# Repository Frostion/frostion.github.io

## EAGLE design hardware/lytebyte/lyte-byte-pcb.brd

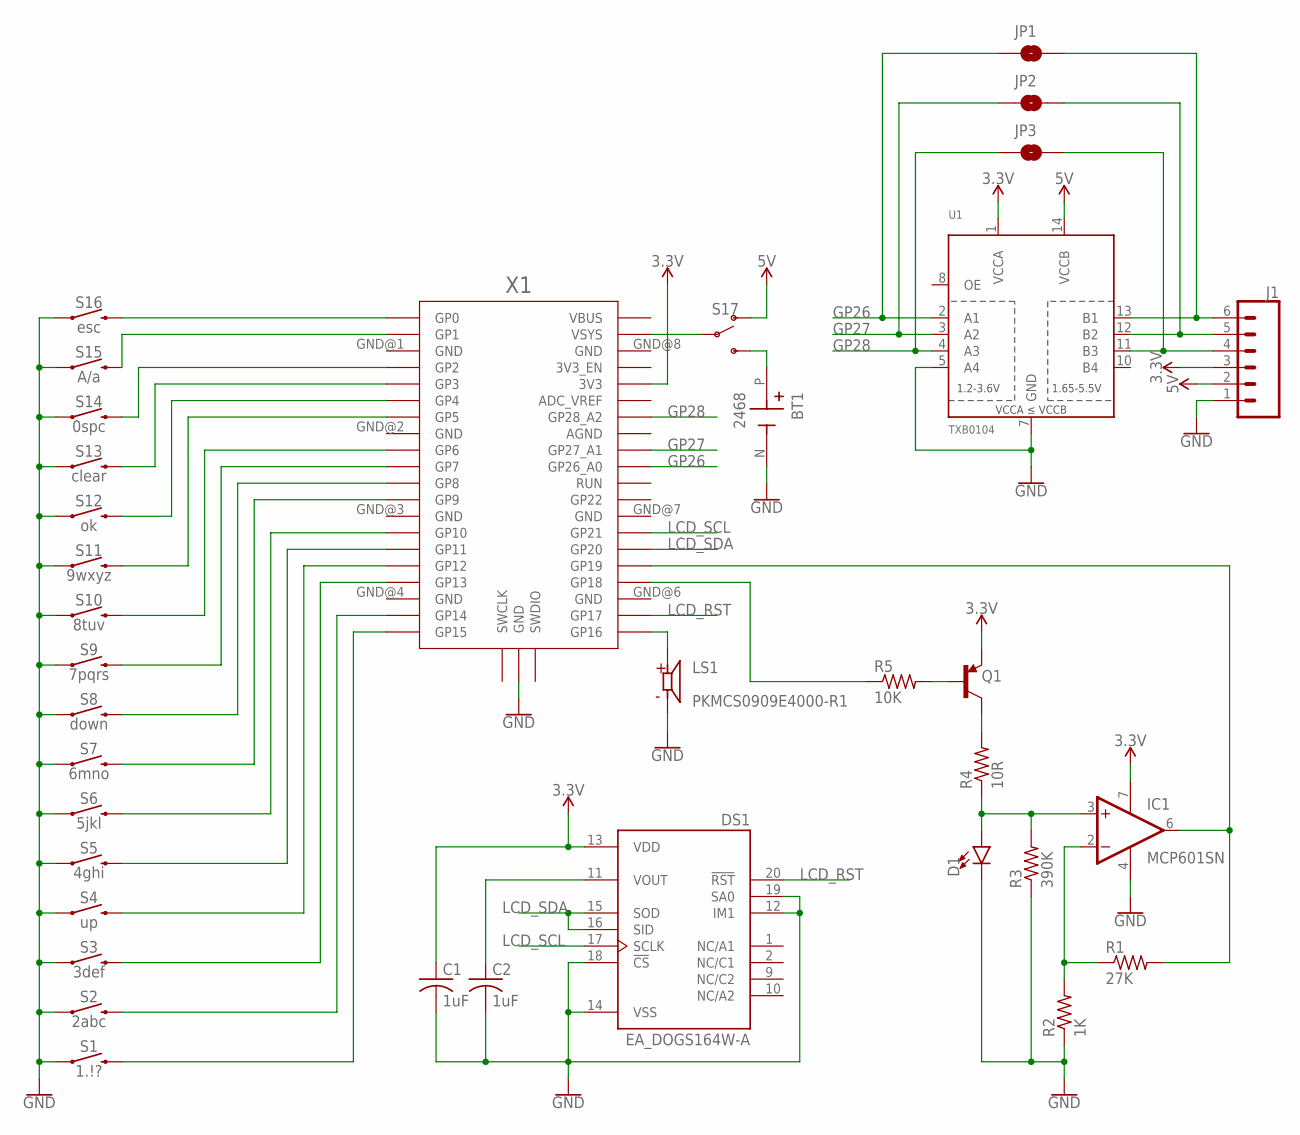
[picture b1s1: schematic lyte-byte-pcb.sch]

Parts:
BT1: 2468; BAT_2468
C1, C2: 1uF; C1206
D1: LED5MM; LED_5MM
DS1: EA_DOGS164W-A; LCD_EA_DOGS164W-A
IC1: MCP601SN; SO08
J1: CONN_06SILK_FEMALE_PTH; 1X06
JP1, JP2, JP3: JUMPER-SMT_2_NO_NO-SILK; SMT-JUMPER_2_NO_NO-SILK
LS1: PKMCS0909E4000-R1; SPKR_PKMCS0909E4000-R1
Q1: TRANS_PNP-PMBT3906|MMBT3906L; SOT23-3
R1: 27K; R1206
R2: 1K; R1206
R3: 390K; R1206
R4: 10R; R1206
R5: 10K; R1206
S1: 1.\!?; TACTILE_SWITCH_SMD_5.2MM
S2: 2abc; TACTILE_SWITCH_SMD_5.2MM
S3: 3def; TACTILE_SWITCH_SMD_5.2MM
S4: up; TACTILE_SWITCH_SMD_5.2MM
S5: 4ghi; TACTILE_SWITCH_SMD_5.2MM
S6: 5jkl; TACTILE_SWITCH_SMD_5.2MM
S7: 6mno; TACTILE_SWITCH_SMD_5.2MM
S8: down; TACTILE_SWITCH_SMD_5.2MM
S9: 7pqrs; TACTILE_SWITCH_SMD_5.2MM
S10: 8tuv; TACTILE_SWITCH_SMD_5.2MM
S11: 9wxyz; TACTILE_SWITCH_SMD_5.2MM
S12: ok; TACTILE_SWITCH_SMD_5.2MM
S13: clear; TACTILE_SWITCH_SMD_5.2MM
S14: 0spc; TACTILE_SWITCH_SMD_5.2MM
S15: A/a; TACTILE_SWITCH_SMD_5.2MM
S16: esc; TACTILE_SWITCH_SMD_5.2MM
S17: SWITCH-SPDT-SMD-AYZ0202; SWITCH_DPDT_SMD_AYZ0202
U1: TXB0104; SO14
X1: RPI_PICO_IG-SMD; RPI_PICO

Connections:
3.3V: C1.1, DS1.13 (VDD), IC1.7 (V+), J1.3, Q1.2 (E), U1.1 (VCCA), X1.3V3
5V: J1.2, S17.1 (O), U1.14 (VCCB)
GND: BT1.N (NEG), C1.2, C2.2, D1.K (C), DS1.12 (IM1), DS1.14 (VSS), DS1.18 (!CS), DS1.19 (SA0), IC1.4 (V-), J1.1, LS1.2 (N), R2.1, R3.1, S1.1, S2.1, S3.1, S4.1, S5.1, S6.1, S7.1, S8.1, S9.1, S10.1, S11.1, S12.1, S13.1, S14.1, S15.1, S16.1, U1.5 (A4), U1.7 (GND), X1.GND@5 (GND)
GP26: JP1.1, U1.2 (A1), X1.GP26_A0
GP27: JP2.1, U1.3 (A2), X1.GP27_A1
GP28: JP3.1, U1.4 (A3), X1.GP28_A2
LCD_RST: DS1.20 (!RST), X1.GP17
LCD_SCL: DS1.17 (SCLK), X1.GP21
LCD_SDA: DS1.15 (SOD), DS1.16 (SID), X1.GP20
LED_TX: IC1.6 (OUT), R1.2, X1.GP19
unnamed: S16.3 (2), X1.GP0
unnamed: S15.3 (2), X1.GP1
unnamed: S14.3 (2), X1.GP2
unnamed: S13.3 (2), X1.GP3
unnamed: S12.3 (2), X1.GP4
unnamed: S11.3 (2), X1.GP5
unnamed: S10.3 (2), X1.GP6
unnamed: S9.3 (2), X1.GP7
unnamed: S8.3 (2), X1.GP8
unnamed: S7.3 (2), X1.GP9
unnamed: S6.3 (2), X1.GP10
unnamed: S5.3 (2), X1.GP11
unnamed: S4.3 (2), X1.GP12
unnamed: S3.3 (2), X1.GP13
unnamed: S2.3 (2), X1.GP14
unnamed: S1.3 (2), X1.GP15
unnamed: C2.1, DS1.11 (VOUT)
unnamed: Q1.1 (B), R5.2
unnamed: Q1.3 (C), R4.2
unnamed: D1.A, IC1.3 (+IN), R3.2, R4.1
unnamed: BT1.P (POS), S17.3 (S)
unnamed: IC1.2 (-IN), R1.1, R2.2
unnamed: S17.2, X1.VSYS
unnamed: R5.1, X1.GP18
unnamed: J1.6, JP1.2, U1.13 (B1)
unnamed: J1.5, JP2.2, U1.12 (B2)
unnamed: J1.4, JP3.2, U1.11 (B3)
unnamed: LS1.1, X1.GP16

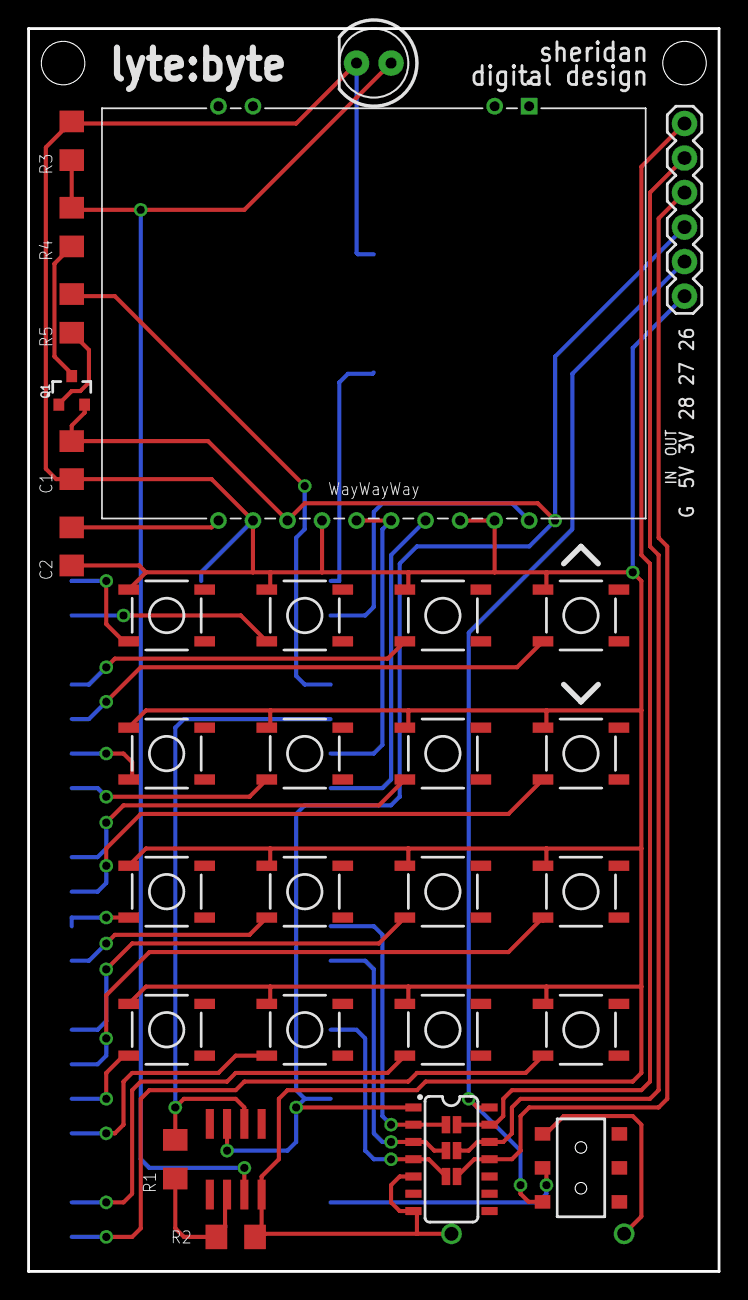
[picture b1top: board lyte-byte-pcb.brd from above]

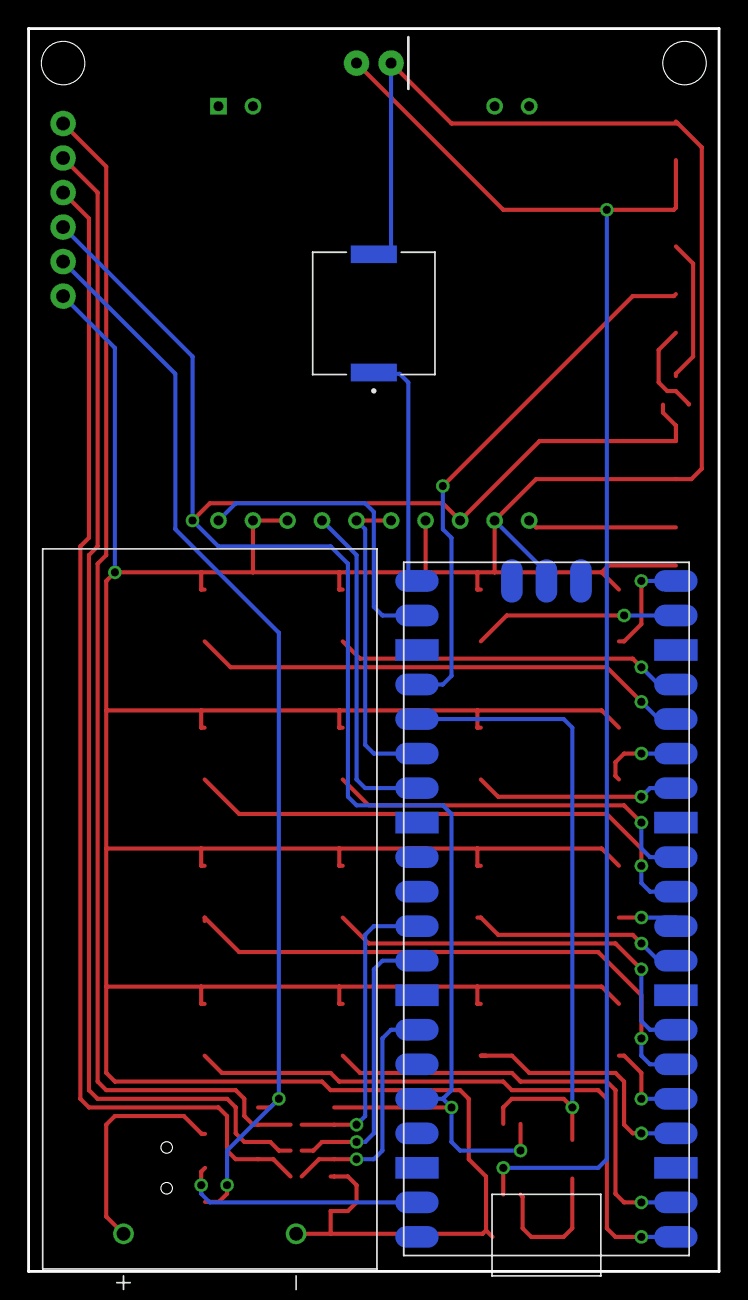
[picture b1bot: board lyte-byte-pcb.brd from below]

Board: 2 copper layers, 50.8 x 91.4 mm, 36 parts (3 on the bottom side), 38 nets.

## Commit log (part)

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2017-02-02 fixxxx
2017-02-02 some GOOD animations now
2017-02-02 github wow
2017-02-02 fixing mistakes github made
2017-02-02 adding CUSTOMIZED placeholders
2017-02-03 no cache
2017-02-03 no caching
2017-02-03 a bit more line height
2017-02-04 Update index.html
    fixed it ;)
2017-02-06 added some table magic
2017-02-06 table magic
2017-02-07 Adding divs
2017-02-07 more div stuff
2017-02-07 Trying to do div stuff
2017-02-07 lets see if this works
2017-02-08 style upgrades
2017-02-13 testing text alignment change
2017-02-13 never mind, going back
2017-02-15 made a page to put other crap in
    man i just have so much content that i needed to make another page for it all
2017-02-15 added "other" link
2017-02-19 uploaded chipwave files
2017-02-21 Starting to add a lil bit of content finally
2017-02-21 holy crap even more content
2017-02-22 i dont even know anymore
2017-02-22 made placeholder page more interesting
2017-02-23 removed direct link to my reddit account
2017-02-23 removed unnecessary page
2017-02-23 I GOT FLEXBOX WORKING YAAAAAAAAY
2017-02-23 mild change
2017-02-23 more mild changes
2017-02-23 SOME WHITESPACE
2017-02-23 a whole bunch of crispy removals
2017-02-23 super cool hover fx
2017-02-24 BETTER placeholder page
2017-02-25 adding content about plushies
2017-02-25 added favicon
2017-02-25 added ratings to plushie page
2017-02-25 added blog link
2017-02-26 A TON OF UPDATES
    Added much more descriptive reviews to the plushies page, and made the
    nav bar work better on smaller screens
2017-02-26 rearranged some pages
    made "plushies and other" page just for plushies, and added a separate
    other page
2017-02-26 added some crap to the "other" page
2017-02-26 better bullet
2017-02-26 new favicon
2017-02-26 newer favicon
2017-02-27 renaming some stuff
2017-02-27 oh god github
2017-02-27 TRYING NEW FONT
2017-02-27 trying another font
2017-02-27 not a good font
2017-02-27 oh god more font
2017-02-27 i think i'm finally there
2017-02-27 removed other page stuff because it was useless
2017-02-27 moved images around
2017-03-01 fresher animations and updates
2017-03-01 un-borked things
2017-03-02 made a nice glow
2017-03-05 better diy synth page layout
2017-03-09 better plushie review layout
    much more readable
2017-03-09 new better pictures and blaziken reivew
2017-03-09 added zoomability to images
2017-03-09 more details
2017-03-10 renamed blaziken image file
2017-03-10 added recommendations to plushie reviews
2017-03-10 removed old images to save memory
2017-03-10 removed crap
2017-03-11 toot
2017-03-11 SLICK NEW homepage
2017-03-11 added buttons to navbar and changed glow
2017-03-12 horizontal rules rule
2017-03-12 RAD NEW BACKGROUND COLORS
2017-03-12 homepage fades in from black now
2017-03-12 made about page bkg more pleasing
2017-03-13 more social media links
2017-03-13 added instagram link
2017-03-13 added a little notification message thing
2017-03-14 notification station test
2017-03-15 removed social media buttons - they were ugly
2017-03-15 removed twitter button
    i dont use twitter
2017-03-15 added a back to top button
2017-03-16 added crap to this page wooooo
2017-03-16 added things i dont like so you can get to know me better
2017-03-16 more things i hate
2017-03-17 more crappppp
2017-03-17 more junk on the about page
2017-03-18 fixed italics
2017-03-18 added padding around images
2017-03-18 cut down on image size
2017-03-19 slightly less ugly green
2017-03-22 changed default text aligns
2017-03-22 changed the look
2017-03-22 removed unneeded align="center"s
2017-03-22 removed unneeded aligns
2017-03-22 woops
2017-03-22 messed up some aligns
2017-03-22 fixed aligns
2017-03-22 added a warning about lack of content
2017-03-28 updated reviews
2017-03-28 review action
2017-03-28 added socially acceptable quotation marks
2017-03-29 why am i doing this
2017-03-29 fixed a mystery parenthesis
2017-03-29 im not ok at grammar
2017-03-31 inches
2017-03-31 added placeholder because IMPATIENT
    COME ON LUCARIO
2017-04-02 new reviews and more images
2017-04-02 removed a gross <hr>
2017-04-02 smaller faster images
2017-04-03 changed some ratings
2017-04-04 added tiny eevee review
2017-04-04 updated palkia arrival day
2017-04-04 ECH GITHUB
2017-04-06 why even
2017-04-06 added placeholder image
2017-04-06 skeleton review added
2017-04-06 palkia arrived!
2017-04-06 fixed encoding & added palkia review
2017-04-08 added palkia review & corrected image cases
2017-04-08 fixed image cases in html file
2017-04-08 fixed hi-res lucario image flipping
2017-04-13 added HYPERLINKS!!!
2017-04-13 minor cosmetic changes
2017-04-13 even MOER cosmetic changes
2017-04-13 fixing my incompetence
2017-04-15 added big eevee review
2017-04-17 review touch-ups
2017-04-17 added another thing I hate
2017-04-18 fixed big eevee link
2017-04-21 ready for more info about synths
2017-04-21 added timer to lucario
2017-04-21 added timer to homepage
2017-04-24 code & circuit for sequin
2017-05-01 getting ready for more reviews
2017-05-06 added cool icons
2017-05-06 woops everything was bold
2017-05-06 added zekrom pics
2017-05-06 added link to plushfresh
2017-05-06 fixed plushfresh link
2017-05-08 Deflated some ratings
2017-05-08 added zekrom review
2017-05-09 updated zekrom review
2017-05-10 removed banner
2017-05-17 mild freshening
2017-05-17 lucario countdown updated
2017-05-18 updated countdown
2017-05-19 getting ready for Lucario review
2017-05-19 added rad 404 page
2017-06-07 working on whole new site
2017-06-07 fixed bkg image on weird screens
2017-06-07 Create CNAME
2017-06-07 more tweaks
2017-06-07 under construction added (yay!)
2017-06-07 i guess
2017-06-08 trying to fix ugly back button
2017-06-08 trying more stuff
2017-06-08 css is awful
2017-06-08 lets try this again
2017-06-08 this is awful
2017-06-08 here we go
2017-06-08 fixing ugly back button
2017-06-08 started adding reviews
2017-06-08 plushie review page looks right now
2017-06-09 updated about page to new style
2017-06-09 added soundcloud link
2017-06-09 more crap on the about page
2017-06-12 added pf link
2017-06-12 created plushfresh page
2017-06-12 added some crap
2017-06-12 more changes
2017-06-13 removed useless crap
2017-06-13 added telegram link
2017-06-17 updates to home & about pages
2017-06-18 updated sona image to have transparent bg
2017-06-18 BEST 404 page
2017-06-18 making it worse
2017-06-19 working wordwrap i hope
2017-06-21 found more music i like
2017-06-24 synthcast page attempt
2017-06-24 better subtitle
2017-07-17 new windows install which is unrelated
2017-08-13 test site
2017-08-13 under construction
2017-08-14 back
2017-08-14 test site update
2017-09-07 new website maybe
2017-09-07 new buttons test
2017-09-07 look how good it looks
2017-09-09 new design
2017-09-10 removed things
2017-09-12 started working on project page
2017-09-13 added social media buttons
2017-09-14 some silly stuff
2017-09-14 new social media buttons
2017-09-25 fixed discord username
2017-10-03 new name, same old dog
2017-10-03 spicy new colors
2017-10-03 Update CNAME
2017-10-03 mobile chrome is happy now
2017-10-04 CUSTOM SCROLLBOYS
2017-10-16 updated discord info
2018-01-18 less bold
2018-03-30 whole new look
2018-03-30 made images smaller
2018-03-30 Revert "made images smaller"
    This reverts commit bd0eb3944fbb7b2654951d91673626944bb9eca1.
2018-03-30 make bkg image smaller
2018-04-09 made image pixely
2018-05-05 sped up animations
2018-05-27 removed gallery section, added android section
2018-12-11 guess what??? new heckin look
2018-12-13 added project page and video hecker page
2019-05-14 fixed social media usernames
2021-04-03 welp everything's changed
2021-04-03 added more info on cedar
2021-04-03 removed cname file
2021-04-03 felt bad for flyynt so i increased his rating
2021-04-03 updated home page icon
2021-04-03 updated durability scores to be more accurate
2021-04-05 fixed grammar
2021-04-07 added adzuki to pool toys menu
2021-04-07 added home page and images for adzuki
2022-03-01 wow cool
2022-03-01 added pool toy photos
2022-03-01 added more info to the pool toys page
2022-03-02 things, and stuff
2022-03-02 hecking windows
2022-03-02 fixed, i hope?
2022-03-04 bean surpeme
2022-03-04 beans
2022-03-05 added vrchat worlds section
2022-04-21 added taco bell item generator
2022-04-21 added lil popup to taco generator
2022-04-22 fixed vrchat link & added more taco bell
2022-04-26 added cybiko stuff
2022-04-29 stufgf
2022-06-08 more pages
2022-06-08 imgages
2022-07-11 chamges
2022-07-15 chambnes
2022-07-19 big changesss
2022-07-19 fixed front page links
2022-07-21 heckj
2022-07-21 heck
2022-07-25 thingjdgpof
2022-07-27 bitmap test
2022-08-03 stuff
2022-08-06 jlkfdg
2022-08-13 404 fix
2022-08-16 oh my god
2022-09-19 draconic ring
2022-09-19 i hate https
2022-09-21 added drakonic to the ring!
2022-10-28 hecky
2022-10-28 sdkjhfg
2022-10-29 netport
2022-10-30 ehck
2022-11-06 new journal entry
2022-11-23 hhhh
2023-03-17 dfdfd
2023-03-17 rawr
2023-03-23 beanb
2023-05-04 henk
2023-06-22 new art
2023-10-05 ikea
2023-11-17 things are different
2023-11-17 added alt text to draconic widget
2023-11-19 bean
2023-12-12 added music page
2024-01-14 added more beans to the webring
2024-01-19 weather
2024-02-09 snacc
2024-02-18 more beans in the ring
2024-02-28 dragon
2024-05-18 overhaul
2024-06-21 remove daily humidity value
2024-06-21 fix NWS icon URL change
2024-09-18 added multimode app
2024-09-27 added speed control

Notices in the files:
parts and their libraries:
SparkFun-LED: Licensing: Creative Commons ShareAlike 4.0 International - https://creativecommons.org/licenses/by-sa/4.0
